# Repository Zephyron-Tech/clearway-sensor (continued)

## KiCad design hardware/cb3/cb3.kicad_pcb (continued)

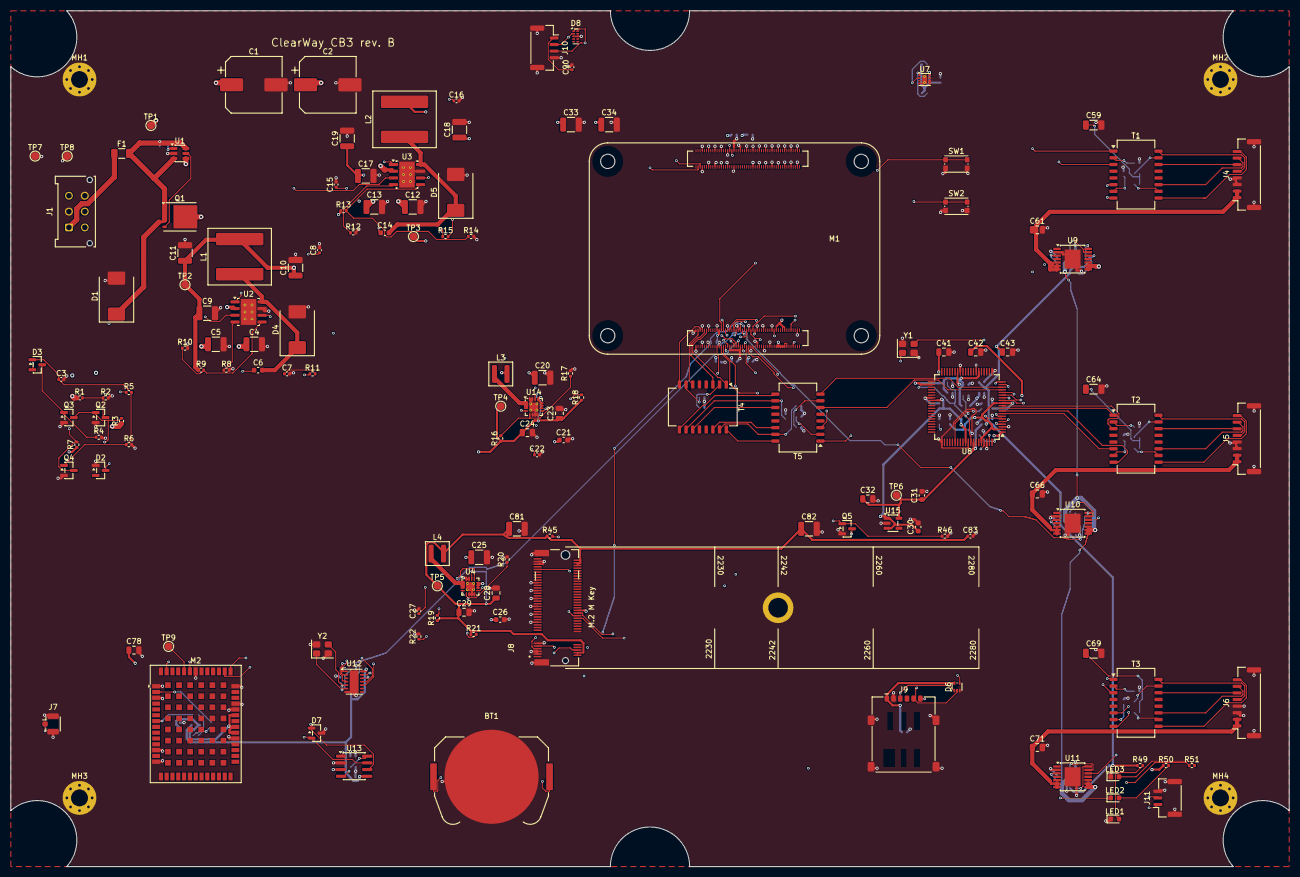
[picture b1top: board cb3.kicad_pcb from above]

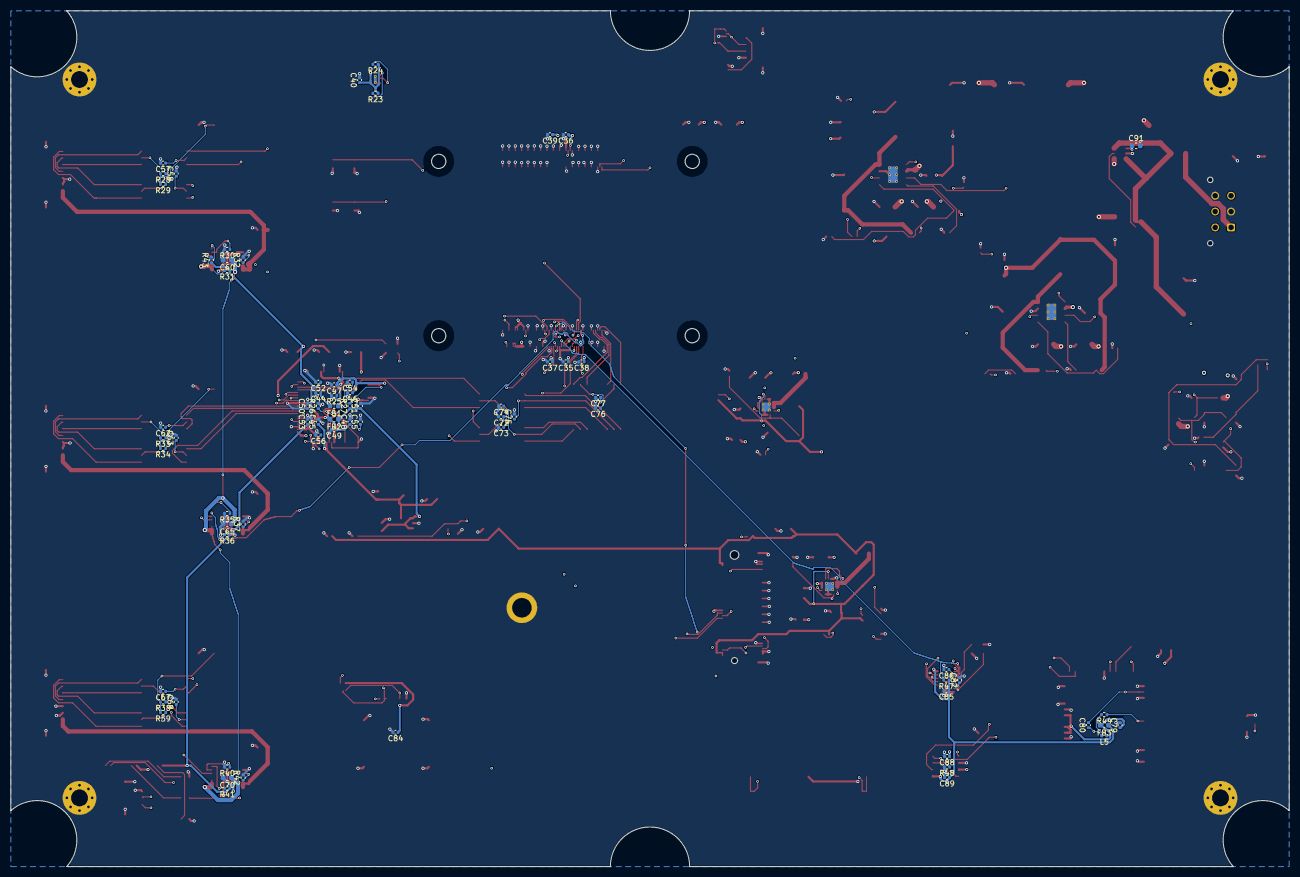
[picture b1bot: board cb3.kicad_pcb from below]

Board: 4 copper layers, 242.0 x 162.0 mm, 214 parts (71 on the bottom side), 163 nets.
